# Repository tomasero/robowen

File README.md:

# RobOwen

    Multimodal input device for IoT infrastucture

### Team
- Alejandro García
- Adam Hutz
- Corten Singer
- Daniel Lim
- Facundo Severi
- Pierluigi Mantovani
- Pierre Karashchuk
- Tomás Vega

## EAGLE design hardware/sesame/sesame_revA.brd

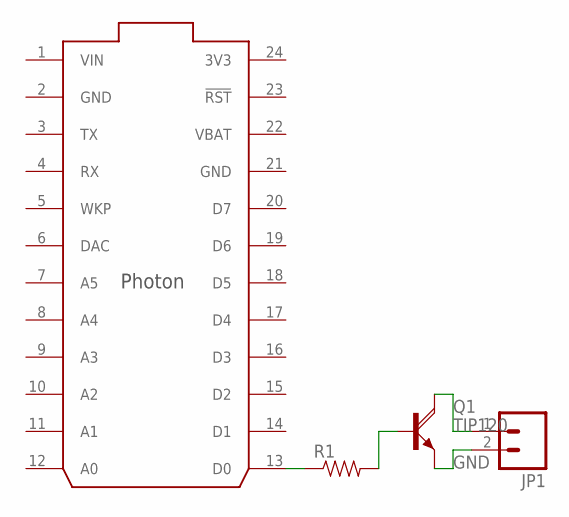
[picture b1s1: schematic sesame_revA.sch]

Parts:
JP1: M02POLAR; MOLEX-1X2
Q1: TIP120; TO220AH
R1: RESISTORPTH-1/4W; AXIAL-0.4
U$1: PHOTON_WITH_HEADERS; PHOTON

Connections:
3V3: U$1.24 (3V3)
GND: JP1.2, Q1.E, U$1.2 (GND), U$1.21 (GND)
unnamed: JP1.1, Q1.C
unnamed: Q1.B, R1.P$2 (2)
unnamed: R1.P$1 (1), U$1.13 (D0)
VBAT: U$1.22 (VBAT)
VIN: U$1.1 (VIN)

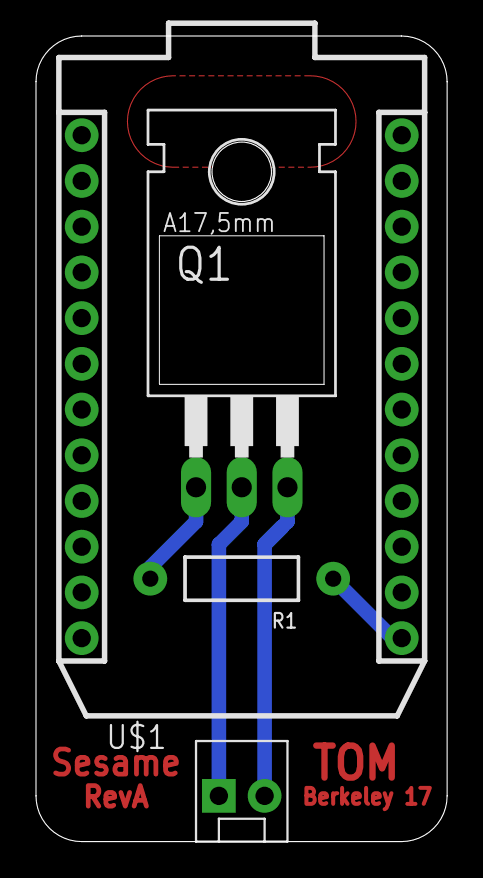
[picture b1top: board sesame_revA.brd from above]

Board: 2 copper layers, 22.8 x 44.8 mm, 4 parts (0 on the bottom side), 4 nets.

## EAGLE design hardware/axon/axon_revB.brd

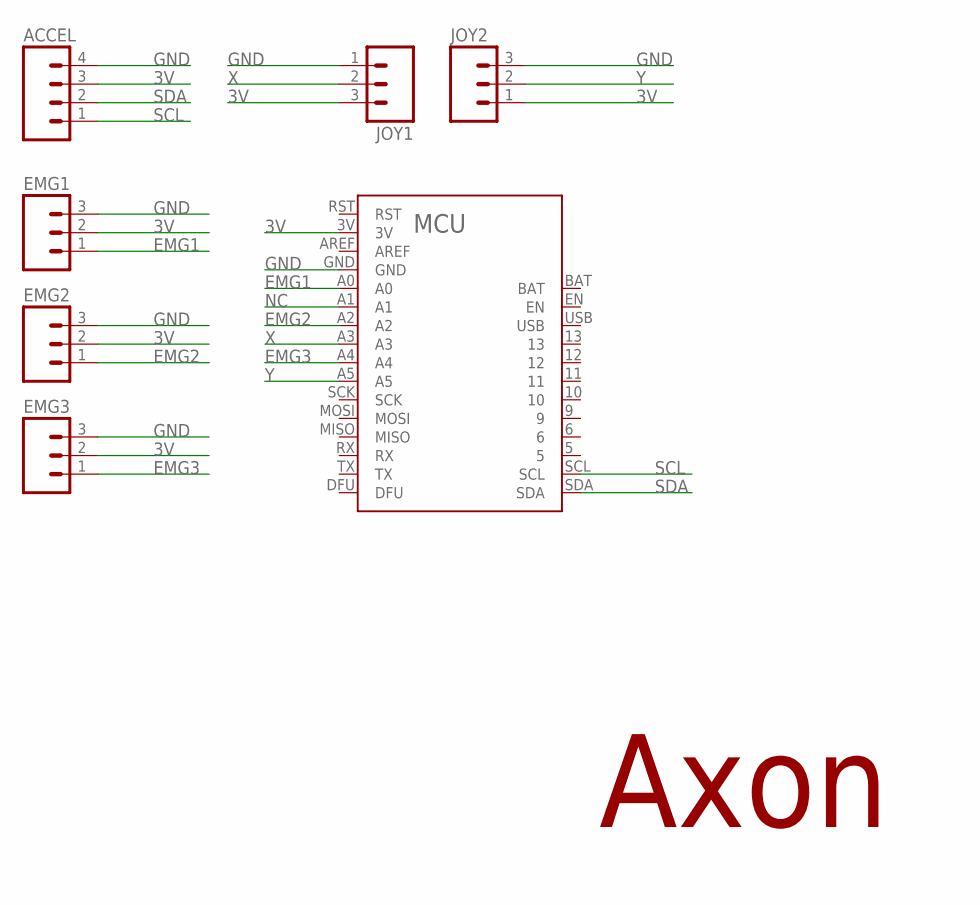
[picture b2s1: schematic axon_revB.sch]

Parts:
ACCEL: M04POLAR; MOLEX-1X4
EMG1, EMG2, EMG3: M03POLAR; MOLEX-1X3
JOY1, JOY2: M03PTH; 1X03
MCU: BLUEFRUIT

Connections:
3V: ACCEL.3, EMG1.2, EMG2.2, EMG3.2, JOY1.3, JOY2.1, MCU.3V
EMG1: EMG1.1, MCU.A0
EMG2: EMG2.1, MCU.A2
EMG3: EMG3.1, MCU.A4
GND: ACCEL.4, EMG1.3, EMG2.3, EMG3.3, JOY1.1, JOY2.3, MCU.GND
NC: MCU.A1
SCL: ACCEL.1, MCU.SCL
SDA: ACCEL.2, MCU.SDA
X: JOY1.2, MCU.A3
Y: JOY2.2, MCU.A5

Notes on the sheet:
Axon

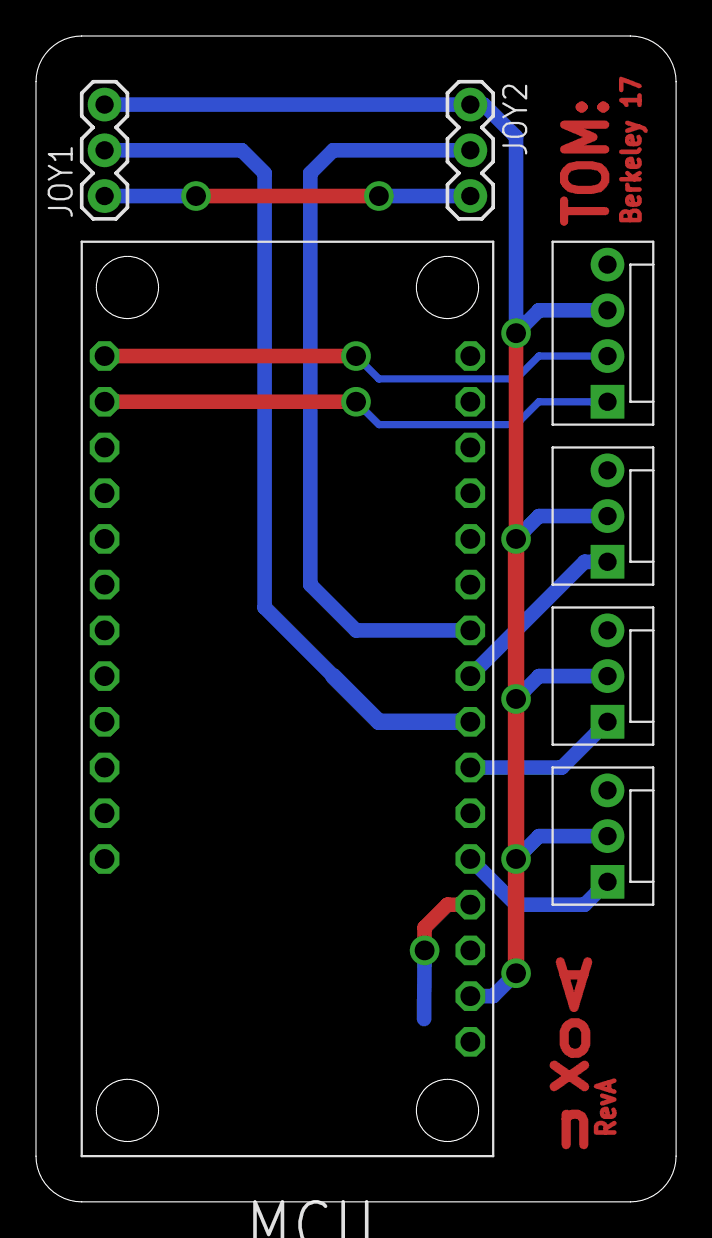
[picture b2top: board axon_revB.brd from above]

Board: 2 copper layers, 35.6 x 64.8 mm, 7 parts (0 on the bottom side), 9 nets.

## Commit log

2017-03-18 README
2017-03-18 ignore python cache files
2017-03-18 server post param parsing works
2017-03-18 Added collect_data scripts and raw_accelerometer data collected from belly
2017-03-18 add client side endpoints + config
2017-03-18 fix config
2017-03-18 update client readme
2017-03-18 refactor send_data
2017-03-18 refactor
2017-03-18 endpoint working! ;
2017-03-18 add print statements
2017-03-18 Arduino folder with Accelerometer file
2017-03-18 Arduino folder with Accelerometer file updated
2017-03-18 make popcorn button
2017-03-18 rename file
2017-03-18 add analysis and arduino code
2017-03-18 add ipython checkpoints to gitignore
2017-03-18 edit analysis
2017-03-18 Added support for EMG data
2017-03-18 Added recursive call for EMG
2017-03-18 add data and myo stuff
2017-03-18 move notebook
2017-03-18 belly popcorn
2017-03-18 update belly test file
2017-03-18 add UI
2017-03-18 add exception handling
2017-03-18 add code to detect emg
2017-03-19 Arduino code for the new mouse
2017-03-19 add log
2017-03-19 Cleaned up code for the arduino mouse control
2017-03-19 cleanup whitespace
2017-03-19 myoware test
2017-03-19 Updated notebook with relative layouts
2017-03-19 move file
2017-03-19 commit test code
2017-03-19 update click code
2017-03-19 change count to millis based delay
2017-03-19 cleaning up UI
2017-03-19 log scrolls down by itself
2017-03-19 working prototype
2017-03-19 driving high frequency data and jupyter notebook to look at accell data
2017-03-19 edit test code
2017-03-19 axon board
2017-03-19 sesame board
2017-03-19 Updated mouse code
2017-03-19 isolation
2017-03-19 text on sesame
2017-03-19 update notebooks I guess
2017-03-19 Nudge Click added
2017-03-19 added code to check if EMG is being held so that owen can turn wheelchair on or off by holding both hands EMG for specific delay time
2017-03-19 images
2017-03-19 heardware images and axon revB with 3V layer fix
2017-03-19 working end to end
2017-03-19 Prettier UI
2017-03-19 Bigger buttons
2017-03-19 update arduino code
2017-03-19 Light slider
2017-03-19 Timestamps on log and open to half screen
2017-03-19 add space
2017-03-19 add test emg power system
2017-03-19 add led code
2017-03-19 fixing sesame
2017-03-19 fixed sesame and extended server side
2017-03-19 merging
2017-03-19 changed name
2017-03-19 Multiple buttons pressed fix
2017-03-19 Server error fixed
2017-03-19 small color change
2017-03-19 change server
2017-04-16 add entry button for changing ip
2017-04-16 update ui

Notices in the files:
parts and their libraries:
SparkFun-Connectors: Licensing: Creative Commons ShareAlike 4.0 International - https://creativecommons.org/licenses/by-sa/4.0
